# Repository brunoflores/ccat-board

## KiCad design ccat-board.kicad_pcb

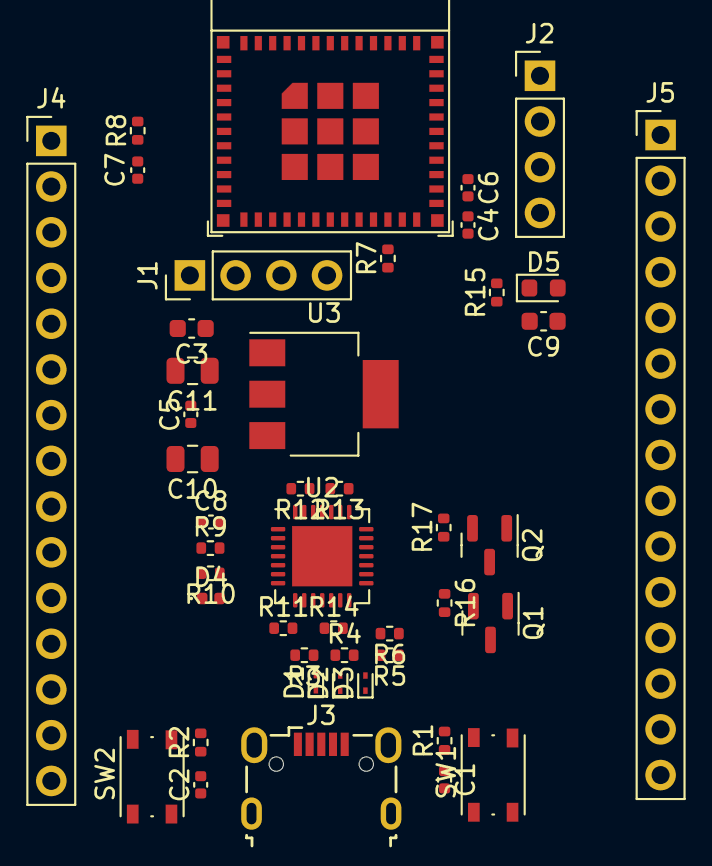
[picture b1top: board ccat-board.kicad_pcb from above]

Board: 2 copper layers, 45 parts (0 on the bottom side), 36 nets, no tracks yet.

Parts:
C1, C2, C5: 0.1uF; C_0402_1005Metric
C3, C9: 10uF; C_0603_1608Metric
C4, C6: 22pF; C_0402_1005Metric
C7, C8: 1uF; C_0402_1005Metric
C10, C11: 22uF; C_0805_2012Metric
D1, D2, D3: ESD9B5.0ST5G; D_SOD-923
D4: D; D_0402_1005Metric
D5: LED; LED_0603_1608Metric
J1: JTAG; PinHeader_1x04_P2.54mm_Vertical
J2: UART; PinHeader_1x04_P2.54mm_Vertical
J3: USB_B_Micro; USB_Micro-B_Wuerth_629105150521
J4, J5: Conn_01x15_Female; PinHeader_1x15_P2.54mm_Vertical
Q1: Q_NPN_BCE; SOT-23
Q2: Q_NPN_BEC; SOT-23
R1, R2, R7, R8, R14, R16, R17: 10K; R_0402_1005Metric
R3, R4, R5, R6, R12, R13: 0; R_0402_1005Metric
R9: 47K5; R_0402_1005Metric
R10: 22K1; R_0402_1005Metric
R11: 1K; R_0402_1005Metric
R15: 1k5; R_0402_1005Metric
SW1, SW2: SW_Push; SW_Push_1P1T_NO_Vertical_Wuerth_434133025816
U1: ESP32-C3-MINI-1-N4; ESP32-C3-MINI-1
U2: CP2102N-A02-GQFN28; QFN-28-1EP_5x5mm_P0.5mm_EP3.35x3.35mm
U3: AMS1117-3.3; SOT-223-3_TabPin2

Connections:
+3.3V: C3.1, C5.1, C9.2, C11.1, J2.1, J4.2, J4.3, R7.1, R8.2, R11.1, R15.1, U1.3 (3V3), U2.6 (VDD), U2.7 (VREGIN), U3.2 (VO)
+5V: D4.1 (K), J4.13, J4.14
/D+: R5.1, R6.1
/D-: R3.1, R4.1
/SW_EN: C1.1, R1.1, SW1.2
/SW_IO9: C2.1, R2.1, SW2.2
DTR: Q2.2 (E), R16.1, U2.28 (~DTR)
EN: C7.1, J4.7, Q1.2 (C), R1.2, R8.1, U1.8 (EN/CHIP_PU)
GND: C1.2, C2.2, C3.2, C4.2, C5.2, C6.2, C7.2, C8.2, C9.1, C10.2, C11.2, D1.2 (A2), D2.2 (A2), D3.2 (A2), D5.1 (K), J2.4, J3.5 (GND), J4.1, J4.6, J4.8, J4.12, J4.15, J5.1, J5.4, J5.7, J5.12, J5.15, R9.2, R14.2, SW1.1, SW2.1, U1.1 (GND), U1.2 (GND), U1.11 (GND), U1.14 (GND), U1.36 (GND), U2.3 (GND), U2.29 (GND), U3.1 (GND)
IO0: J4.9, U1.12 (GPIO0/ADC1_CH0/XTAL_32K_P)
IO1: J4.10, U1.13 (GPIO1/ADC1_CH1/XTAL_32K_N)
IO2: J4.4, U1.5 (GPIO2/ADC1_CH2)
IO3: J4.5, U1.6 (GPIO3/ADC1_CH3)
IO4: J1.1, J5.11, U1.18 (GPIO4/ADC1_CH4)
IO5: J1.2, J5.10, U1.19 (GPIO5/ADC2_CH0)
IO6: J1.3, J5.9, U1.20 (GPIO6)
IO7: J1.4, J5.8, U1.21 (GPIO7)
IO8: J5.6, R7.2, U1.22 (GPIO8)
IO9: J5.5, Q2.3 (C), R2.2, U1.23 (GPIO9)
IO10: J4.11, U1.16 (GPIO10)
IO18: C4.1, D2.1 (A1), J3.2 (D-), J5.13, R4.2, U1.26 (GPIO18/USB_D-)
IO19: C6.1, D3.1 (A1), J3.3 (D+), J5.14, R5.2, U1.27 (GPIO19/USB_D+)
unnamed: C8.1, R9.1, R10.2, U2.8 (VBUS)
unnamed: D5.2 (A), R15.2
unnamed: Q1.1 (B), R16.2
unnamed: Q2.1 (B), R17.2
unnamed: R11.2, U2.9 (~RST)
unnamed: R12.1, U2.26 (TXD)
unnamed: R13.2, U2.25 (RXD)
unnamed: R14.1, U2.11 (~SUSPEND)
RTS: Q1.3 (E), R17.1, U2.24 (~RTS)
U0RXD: J2.3, J5.3, R12.2, U1.30 (GPIO20/U0RXD)
U0TXD: J2.2, J5.2, R13.1, U1.31 (GPIO21/U0TXD)
USB_DN: R3.2, U2.5 (D-)
USB_DP: R6.2, U2.4 (D+)
VBUS: C10.1, D1.1 (A1), D4.2 (A), J3.1 (VBUS), R10.1, U3.3 (VI)

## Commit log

2022-07-09 Add files.
